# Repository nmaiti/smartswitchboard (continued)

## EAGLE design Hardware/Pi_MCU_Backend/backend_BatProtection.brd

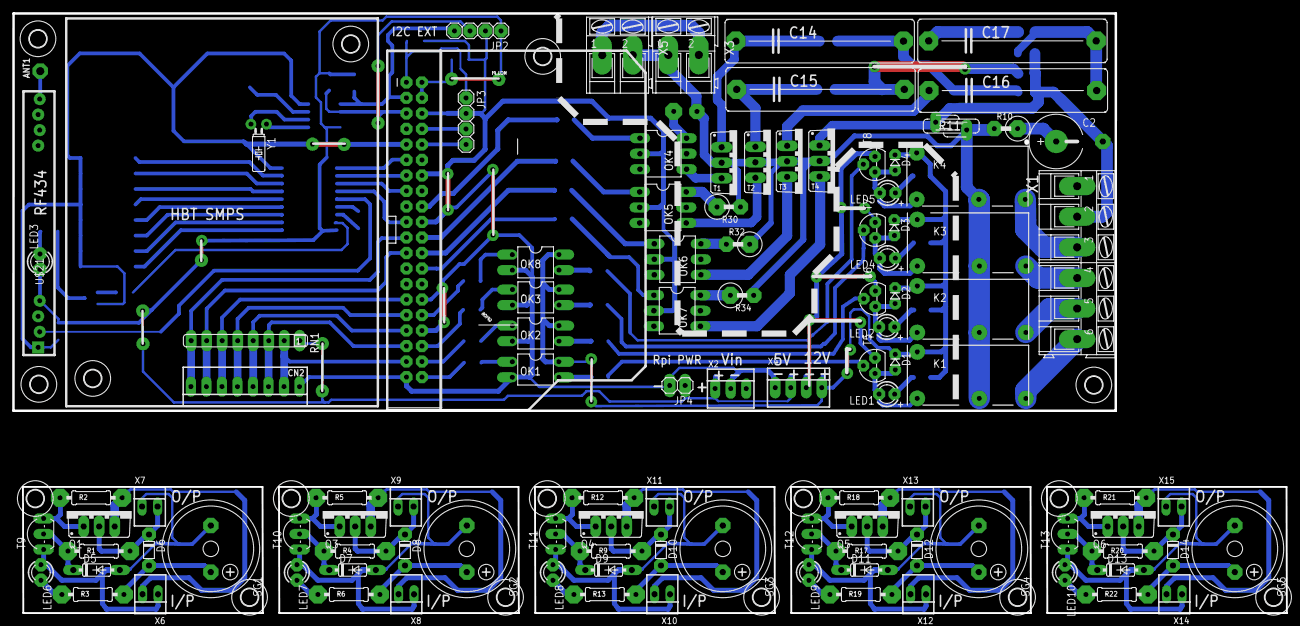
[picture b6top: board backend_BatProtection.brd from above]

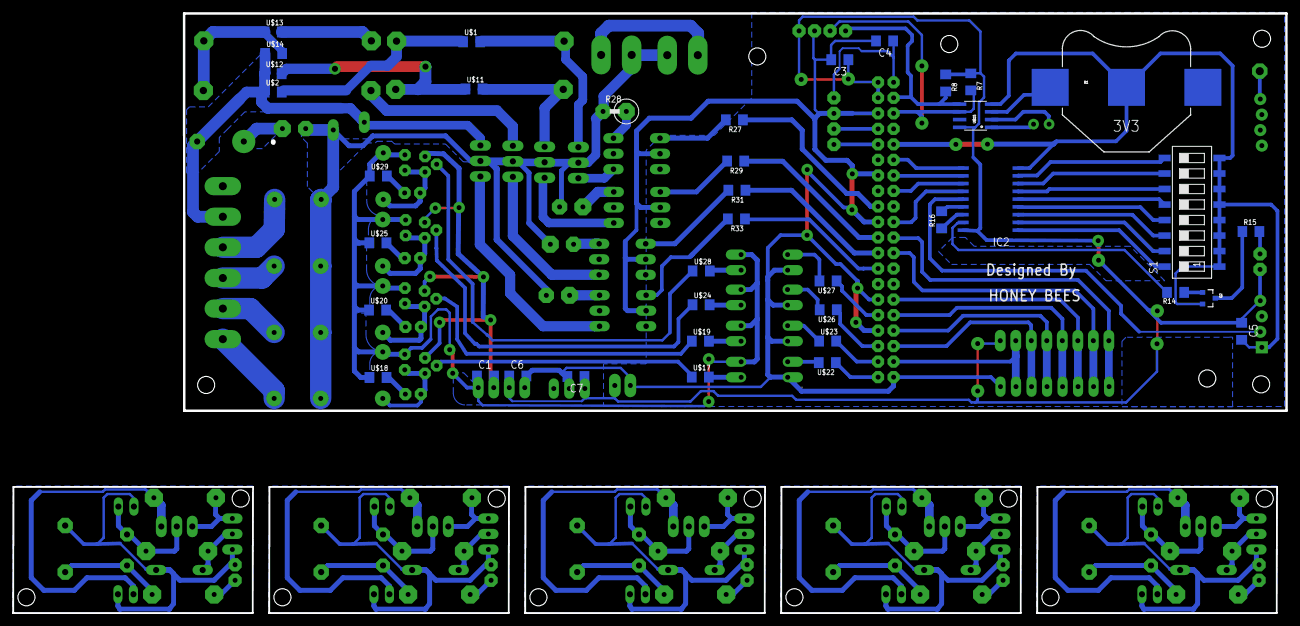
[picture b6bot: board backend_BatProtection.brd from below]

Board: 2 copper layers, 208.5 x 98.2 mm, 163 parts (39 on the bottom side), 128 nets.

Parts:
ANT1: PAD-01
B1: BATTCON_20MM
C1, C3, C4, C5, C6, C7: C1206
C2: E5R
C14, C16: 2.2uF/250VAC; C27.5B9
C15, C17: 3.3uF/250VAC; C27.5B9
CN2: Capsense I/P; 22-23-2081
D1, D2, D3, D4: D-2.5
D5, D7, D9, D11, D13: 1N4148DO35-7; DO35-7
D6, D8, D10, D12, D14: D-5
IC2: HT680D; SOP18
JP1: RASPBERRYPI-B+-GPIO; 2X20-SHROUDED
JP2, JP3: 1X04
JP4: 1X02
K1, K2, K3, K4: RE030012; RE-SCHRACK
LED1, LED2, LED3, LED4, LED5, LED6, LED7, LED8, LED9, LED10: LED3MM
OK1, OK2, OK3, OK8: PC817; DIL04
OK4, OK5, OK6, OK7: MOC3041M; DIL06
Q1, Q3, Q4, Q5, Q6: IRF540; TO220BV
Q2: MMBT2222A; SOT23-3
R1, R2, R3, R4, R5, R6, R9, R12, R13, R17, R18, R19, R20, R21, R22: 0207/10
R7, R8: 4k7; 1206
R10: 0411V
R11: S07K11
R14: 10K; 1206
R15, R27, R29, R31, R33: 560R; 1206
R16: 33k; 1206
R28, R30, R32, R34: 470R/0.5W; 0411V
RN1: SIL8
S1: SWS008; SMS-008
SG1, SG2, SG3, SG4, SG5: F/HMB
T1, T2, T3, T4: BTB16-V; TO220BV
T5, T6, T7, T8: BC547; TO92
T9, T10, T11, T12, T13: TO92-EBC
U$1, U$11, U$13: 220K; 1206
U$2, U$12, U$14: 2E2; 1206
U$3, U$4, U$5, U$6, U$7, U$8, U$9, U$10, U$16, U$30, U$31, U$32, U$33, U$34, U$35, U$36: 2,8
U$15: DS1307SO8; SO08
U$17, U$18, U$19, U$20, U$22, U$23, U$24, U$25, U$26, U$27, U$28, U$29: 1k; 1206
U$21: RF-LINK_RX
X1: AK300/6
X2: 22-23-2031
X3, X5: AK300/2
X4: 22-23-2041
X6, X7, X8, X9, X10, X11, X12, X13, X14, X15: 22-23-2021
Y1: 32.768KHz; TC26H

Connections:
(DIN)TE: IC2.14, U$21.DATA@1
(VT)ADOUT: IC2.17, R14.2
+: Q1.S, R2.2, X6.2
+1: Q3.S, R5.2, X8.2
+2: Q4.S, R12.2, X10.2
+3: Q5.S, R18.2, X12.2
+3V3: C4.1, JP1.1, JP1.17, JP3.1
+4: Q6.S, R21.2, X14.2
+5V: C3.1, C5.1, C6.1, C7.1, IC2.18, JP1.2, JP1.4, JP2.1, JP4.1, LED3.A, R7.1, R8.1, RN1.1, U$15.8, U$21.+5V@1, X2.1, X4.2
+12V: C1.1, D1.C, D2.C, D3.C, D4.C, K1.A2, K2.A2, K3.A2, K4.A2, OK1.4, OK2.4, OK3.4, OK8.4, U$18.1, U$20.1, U$25.1, U$29.1, X4.4
-12V: C1.2, T5.1, T6.1, T7.1, T8.1, X4.3
A0: IC2.1, S1.16
A1: IC2.2, S1.15
A2: IC2.3, S1.14
A3: IC2.4, S1.13
A4: IC2.5, S1.12
A5: IC2.6, S1.11
A6: IC2.7, S1.10
A7: IC2.8, S1.9
DOWN: CN2.7, JP1.23, RN1.7
FAN_ON/OFF: CN2.8, JP1.21, RN1.8
FAN_REG: C2.-, R11.1, T4.T1, U$2.1, U$12.1, U$14.1, X1.2
G: D5.A, LED6.A, SG1.-, T9.E, X6.1, X7.1
G1: D7.A, LED7.A, SG2.-, T10.E, X8.1, X9.1
G2: D9.A, LED8.A, SG3.-, T11.E, X10.1, X11.1
G3: D11.A, LED9.A, SG4.-, T12.E, X12.1, X13.1
G4: D13.A, LED10.A, SG5.-, T13.E, X14.1, X15.1
GND: B1.2, C3.2, C4.2, C5.2, C6.2, C7.2, CN2.1, IC2.9, JP1.6, JP1.9, JP1.14, JP1.20, JP1.25, JP1.30, JP1.34, JP1.39, JP2.2, JP3.2, JP4.2, OK1.2, OK2.2, OK3.2, OK4.2, OK5.2, OK6.2, OK7.2, OK8.2, Q2.2, S1.1, S1.2, S1.3, S1.4, S1.5, S1.6, S1.7, S1.8, U$15.4, U$21.GND@1, X2.2, X4.1
L1: JP1.40, U$22.1
L2: JP1.38, U$23.2
L3: JP1.36, U$26.1
L4: JP1.32, U$27.1
LEVEL1: JP1.18, R27.1
LEVEL2: JP1.22, R29.1
LEVEL3: JP1.24, R31.1
LEVEL4: JP1.26, R33.1
LINE: K1.14, K2.14, K3.14, K4.14, R10.2, R11.2, R28.2, R30.2, R32.1, R34.2, T1.T2, T2.T2, T3.T2, T4.T2, X3.1, X5.2
unnamed: OK6.1, R31.2
unnamed: OK4.1, R27.2
unnamed: OK5.1, R29.2
unnamed: OK4.6, R28.1
unnamed: OK7.1, R33.2
unnamed: OK1.3, U$17.2
unnamed: T5.2, U$17.1
unnamed: D1.A, K1.A1, LED1.K, T5.3
unnamed: LED1.A, U$18.2
unnamed: OK1.1, U$22.2
unnamed: U$15.2, Y1.2
unnamed: OK2.1, U$23.1
unnamed: OK2.3, U$19.2
unnamed: T6.2, U$19.1
unnamed: C2.+, R10.1
unnamed: D2.A, K2.A1, LED2.K, T6.3
unnamed: Q2.1, R14.1
unnamed: U$15.1, Y1.1
unnamed: K3.11, X1.4
unnamed: B1.1, U$15.3
unnamed: Q2.3, R15.1
unnamed: LED2.A, U$20.2
unnamed: K1.11, X1.6
unnamed: LED3.K, R15.2
unnamed: K2.11, X1.5
unnamed: OK5.6, R30.1
unnamed: OK6.6, R32.2
unnamed: ANT1.1, U$21.ANT
unnamed: OK3.1, U$26.2
unnamed: OK8.3, U$28.2
unnamed: OK7.6, R34.1
unnamed: OK3.3, U$24.2
unnamed: T7.2, U$24.1
unnamed: T8.2, U$28.1
unnamed: D3.A, K3.A1, LED4.K, T7.3
unnamed: K4.11, X1.3
unnamed: LED4.A, U$25.2
unnamed: D4.A, K4.A1, LED5.K, T8.3
unnamed: LED5.A, U$29.2
unnamed: OK8.1, U$27.2
unnamed: Q1.G, R2.1, T9.C
unnamed: D6.C, Q1.D, R1.2, X7.2
unnamed: D5.C, R1.1, T9.B
unnamed: Q3.G, R5.1, T10.C
unnamed: D6.A, R3.2, SG1.+
unnamed: LED6.K, R3.1
unnamed: D8.C, Q3.D, R4.2, X9.2
unnamed: D7.C, R4.1, T10.B
unnamed: D8.A, R6.2, SG2.+
unnamed: OK4.4, T1.G
unnamed: C14.1, T1.T1, U$1.2
unnamed: C14.2, U$1.1, U$2.2
unnamed: LED7.K, R6.1
unnamed: Q4.G, R12.1, T11.C
unnamed: D10.C, Q4.D, R9.2, X11.2
unnamed: D9.C, R9.1, T11.B
unnamed: OK5.4, T2.G
unnamed: C15.1, T2.T1, U$11.2
unnamed: C15.2, U$11.1, U$12.2
unnamed: D10.A, R13.2, SG3.+
unnamed: LED8.K, R13.1
unnamed: Q5.G, R18.1, T12.C
unnamed: D12.C, Q5.D, R17.2, X13.2
unnamed: OK6.4, T3.G
unnamed: C16.1, C17.1, T3.T1, U$13.2
unnamed: C16.2, C17.2, U$13.1, U$14.2
unnamed: D11.C, R17.1, T12.B
unnamed: D12.A, R19.2, SG4.+
unnamed: LED9.K, R19.1
unnamed: Q6.G, R21.1, T13.C
unnamed: OK7.4, T4.G
unnamed: D14.C, Q6.D, R20.2, X15.2
unnamed: D13.C, R20.1, T13.B
unnamed: D14.A, R22.2, SG5.+
unnamed: LED10.K, R22.1
NEUTRAL: X1.1, X3.2, X5.1
OSC1: IC2.16, R16.1
OSC2: IC2.15, R16.2
RFD0: IC2.10, JP1.11
RFD1: IC2.11, JP1.13
RFD2: IC2.12, JP1.15
RFD3: IC2.13, JP1.19
RX: JP1.10, JP3.4
SCL: JP1.5, JP2.3, R7.2, U$15.6
SDA: JP1.3, JP2.4, R8.2, U$15.5
SW-1: CN2.2, JP1.37, RN1.2
SW-2: CN2.3, JP1.35, RN1.3
SW-3: CN2.4, JP1.33, RN1.4
SW-4: CN2.5, JP1.31, RN1.5
TX: JP1.8, JP3.3
UP: CN2.6, JP1.29, RN1.6

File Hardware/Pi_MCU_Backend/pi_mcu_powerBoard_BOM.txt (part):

Partlist exported from F:/Honey Bee's/smartswitchboard/Hardware/Pi_MCU_Backend/pi_mcu_powerBoard.sch at 05-09-2016 00:49:13

Part Value               Device                  Package       Description                                                                MF                      MPN          OC_FARNELL OC_NEWARK PROD_ID     VALUE    
ANT1                     ANTENNA                 PAD-01        Antenna                                                                                                                                                   
B1                       BATTERY20SMD            BATTCON_20MM  Battery Holders                                                                                                                                           
C1                       C-EUC1206               C1206         CAPACITOR, European symbol                                                                                                                                
C2                       CPOL-USE5-9VAXIAL       E5R           POLARIZED CAPACITOR, American symbol                                                                                                                      
C3                       C-EUC1206               C1206         CAPACITOR, European symbol                                                                                                                                
C4                       C-EUC1206               C1206         CAPACITOR, European symbol                                                                                                                                
C5                       C-USC1206               C1206         CAPACITOR, American symbol                                                                                                                                
C6                       C-EUC1206               C1206         CAPACITOR, European symbol                                                                                                                                
C7                       C-EUC1206               C1206         CAPACITOR, European symbol                                                                                                                                
C14  2.2uF/250VAC        C27/9                   C27.5B9       CAPACITOR                                                                                                                                                 
C15  3.3uF/250VAC        C27/9                   C27.5B9       CAPACITOR                                                                                                                                                 
C16  2.2uF/250VAC        C27/9                   C27.5B9       CAPACITOR                                                                                                                                                 
C17  3.3uF/250VAC        C27/9                   C27.5B9       CAPACITOR                                                                                                                                                 
CN2  Capsense I/P        22-23-2081              22-23-2081    .100" (2.54mm) Center Header - 8 Pin                                       MOLEX                   22-23-2081   1756826    01C7592                        
D1                       DIODE-D-2.5             D-2.5         DIODE                                                                                                                                                     
D2                       DIODE-D-2.5             D-2.5         DIODE                                                                                                                                                     
D3                       DIODE-D-2.5             D-2.5         DIODE                                                                                                                                                     
D4                       DIODE-D-2.5             D-2.5         DIODE                                                                                                                                                     
D5   1N4148DO35-7        1N4148DO35-7            DO35-7        DIODE                                                                                                                                                     
D6                       DIODE-D-5               D-5           DIODE                                                                                                                                                     
IC2  HT680D              HT680D                  SOP18         318 Series of Encoders TE trigger type                                                                          unknown    unknown                        
JP1  RASPBERRYPI-B+-GPIO RASPBERRYPI-B+-GPIO     2X20-SHROUDED Raspberry Pi B+ GPIO Header                                                                                                                               
JP2                      PINHD-1X4               1X04          PIN HEADER                                                                                                                                                
JP3                      PINHD-1X4               1X04          PIN HEADER                                                                                                                                                
JP4                      PINHD-1X2               1X02          PIN HEADER                                                                                                                                                
K1   RE030012            RE030012                RE-SCHRACK    Miniature PCB Relay 1 pole 6 A SCHRACK                                     TYCO ELECTRONICS        RE030012     515840     17M1743                        
K2   RE030012            RE030012                RE-SCHRACK    Miniature PCB Relay 1 pole 6 A SCHRACK                                     TYCO ELECTRONICS        RE030012     515840     17M1743                        
K3   RE030012            RE030012                RE-SCHRACK    Miniature PCB Relay 1 pole 6 A SCHRACK                                     TYCO ELECTRONICS        RE030012     515840     17M1743                        
K4   RE030012            RE030012                RE-SCHRACK    Miniature PCB Relay 1 pole 6 A SCHRACK                                     TYCO ELECTRONICS        RE030012     515840     17M1743                        
LED1                     LED3MM                  LED3MM        LED                                                                                                                                                       
LED2                     LED3MM                  LED3MM        LED                                                                                                                                                       
LED3                     LED3MM                  LED3MM        LED                                                                                                                                                       
LED4                     LED3MM                  LED3MM        LED                                                                                                                                                       
LED5                     LED3MM                  LED3MM        LED                                                                                                                                                       
LED6                     LED3MM                  LED3MM        LED                                                                                                                                                       
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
